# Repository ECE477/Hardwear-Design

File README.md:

# Hardwear Design
Schematic and PCB

## PCB Checklist
### 1 Parts Completion Check
- [x] All major componenets included (ie. Micro, Power Supply, Regulation, Battery Management, IMU, GPS, LoRa, TOLED, Push Buttons, Reset Button, Signal LEDS)
- [x] All support components included (ie. Micro minimum connections, Testing Circuit, Support components package and value(R,Caps,Ind), Application circuits)
#### Other
- [x] Progamming Header 
- [x] Reset Circuit
- [x] Power Connectors
- [x] Mounting holes
- [x] Heartbeat LED
- [x] Debugging LEDs (Transmit LED)
### 2 PCB Footprint Verification Check
- [x] All parts fir on 1:1 scale printout of PCB
### 3 Parts Placement Check
- [x] Oscillator close to Micro? (N/A)
- [x] Decoupling caps close to/under related ICs?
- [x] Connectors on board edges?
- [x] Parts grouped by system and/or in reasonable way that minimizes routing?
### 4 Mechanical/Space Conflict Check:
- [x] Has x- and y- footprint space around electrical pins and pads of all parts been accounted for?
- [x] Has z-height of all parts been accounted for?
- [x] Has clearance been provided for the bolt heads of all mounting holes?
- [x] Have connectors been placed on the outer edges of boards where appropriate? Are they overhanging edges of boards where appropriate? Are they oriented in the correct direction?
- [x] Are all mounting and mechanical support holes free of traces and other electrical items?
### 5 Routing Completion Check:
- [x] All traces routed? (In Eagle, the ratsnest command will say “nothing to do”)
- [x] Oscillator traces clear of interfering signals?
- [x] Traces of appropriate widths to handle current being passed? (Including power traces)
- [x] Traces entering pads at 90-degree angles (or 45 degree angles, where appropriate)?
### 6 Routing Minimization Check:
- [x] Trace lengths have been minimized where possible?
- [x] Octagonal (45-degree constrained) layout mode has been utilized, where possible?
- [x] Right angles have been removed, except where necessary?
- [x] Acute angles have been eliminated from all board routing?
### 7 Via Minimization Check:
- [x] Vias have been eliminated to extent reasonable?
- [x] Signal planes on opposite sides of boards are connected by vias at reasonable intervals?
- [x] Signal Plane Check:
- [x] Signal planes have been included, where reasonable?
- [x] Analog ground (AGND), has been separated from the main ground net in accordance with microcontroller datasheets?
- [x] Isolation on all signal planes has been set to at least 12 mils?
### 9 Silkscreen check
- [x] Silkscreen labels have been provided for all component IDs and connector signal names?
- [x] Silkscreen labels have been appropriately placed near components, but not on top of pads or pins?
- [x] Pin 1 of all ICs and other polarity-sensitive components (such as diodes) is clearly marked?
- [x] Board silkscreen layer includes course and team number "ECE477 Group <x>"?
- [x] Board silkscreen layer includes names of all team members, if possible?
- [x] Board silkscreen layer includes a descriptive name to identify the board?
- [x] Board silkscreen layer includes a revision number and/or last modified date?
### 10 Gerber Check
- [x] Gerber files have been inspected by a gerber viewer program (e.g. gerbv) to check for any
last-minute software CAM-processing defects

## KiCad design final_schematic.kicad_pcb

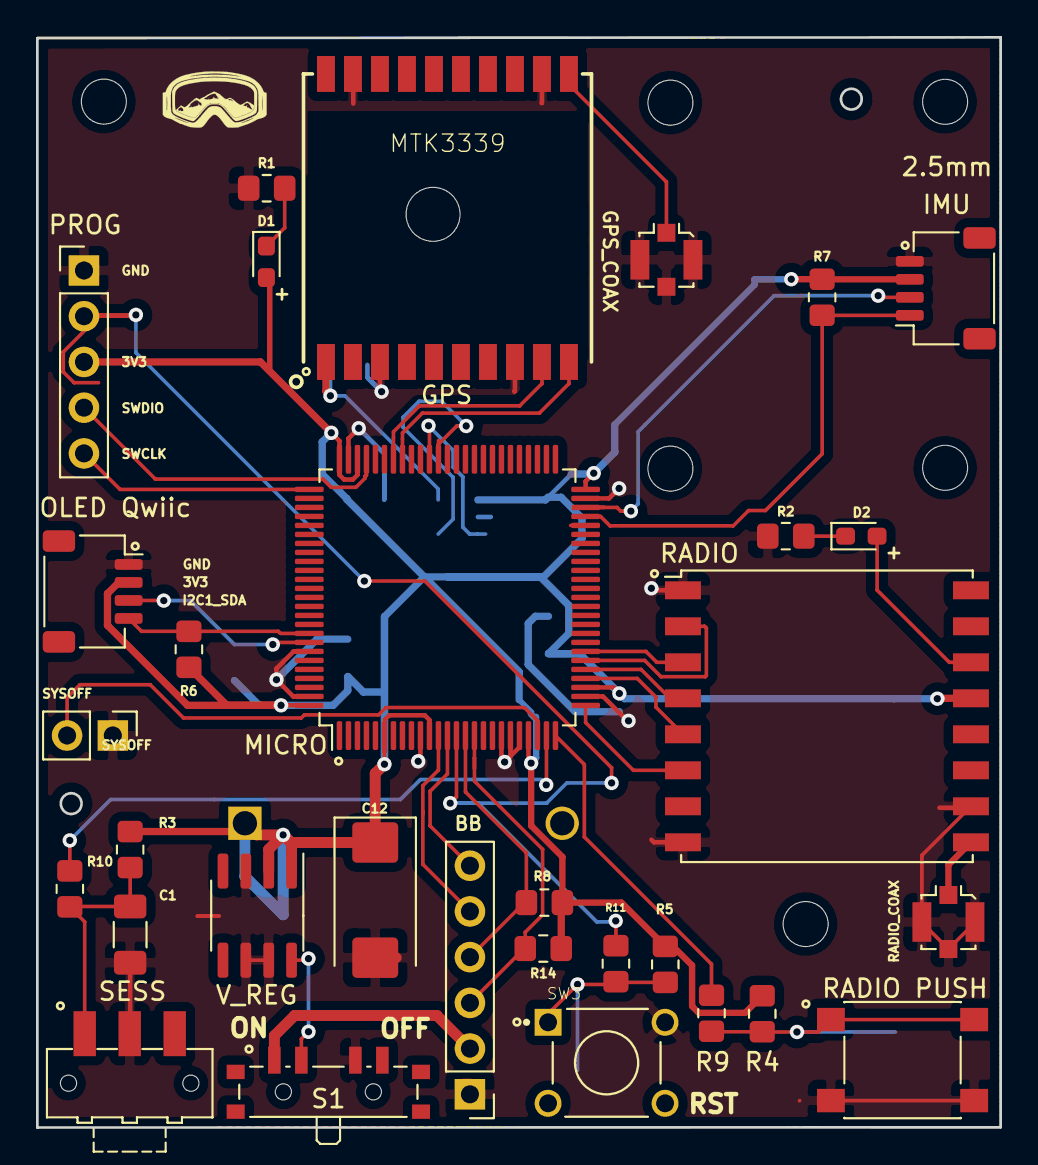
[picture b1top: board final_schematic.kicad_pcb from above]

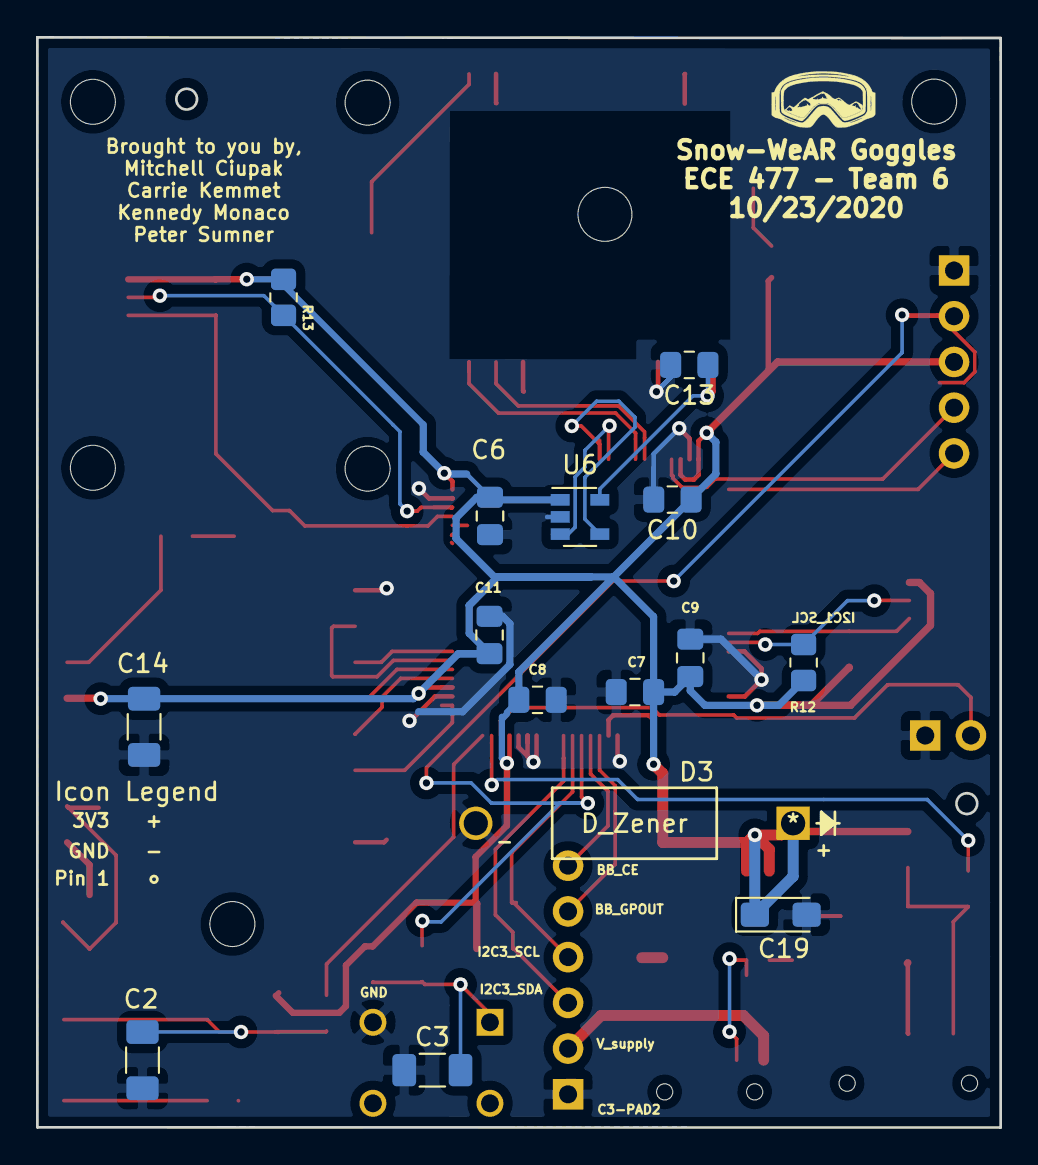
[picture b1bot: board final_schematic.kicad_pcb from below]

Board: 2 copper layers, 53.5 x 60.6 mm, 47 parts (15 on the bottom side), 36 nets.

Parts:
2.5mm: 2.5mm; MountingHole_2.5mm
BB: Battery Babysitter; PinHeader_1x06_P2.54mm_Vertical
C1, C2, C3: 1uF; C_1206_3216Metric_Pad1.33x1.80mm_HandSolder
C6, C7, C8, C9, C10, C11, C13: 0.1uF; C_0805_2012Metric_Pad1.18x1.45mm_HandSolder
C12: 3.3uF; CP_EIA-7343-15_Kemet-W_Pad2.25x2.55mm_HandSolder
C14: 10uF; C_1206_3216Metric_Pad1.33x1.80mm_HandSolder
C19: .1uF; CP_EIA-3216-10_Kemet-I_Pad1.58x1.35mm_HandSolder
D1: LED_HEARTBEAT_R1; D_0603_1608Metric_Pad1.05x0.95mm_HandSolder
D2: LED_TRANSMIT_G1; D_0603_1608Metric_Pad1.05x0.95mm_HandSolder
D3: D_Zener; 1N5355BRLG
GPS: MTK3339; FGPMMOPA6H
IMU: IMU_QWIIC; JST_SH_SM04B-SRSS-TB_1x04-1MP_P1.00mm_Horizontal
J8: GPS_COAX; U.FL_Molex_MCRF_73412-0110_Vertical
MICRO: STM32L476VGTx; LQFP-100_14x14mm_P0.5mm
OLED Qwiic: OLED Qwiic; JST_SH_SM04B-SRSS-TB_1x04-1MP_P1.00mm_Horizontal
PROG: PROG; PinHeader_1x05_P2.54mm_Vertical
R1, R2, R9, R10, R11: 62; R_0805_2012Metric_Pad1.20x1.40mm_HandSolder
R3, R4, R5, R6, R7, R8, R12, R13, R14: 10k; R_0805_2012Metric_Pad1.20x1.40mm_HandSolder
RADIO: RFM95W-868S2; HOPERF_RFM9XW_SMD
RADIO PUSH: SW_Push_RADIO; SW_SPST_PTS645
RADIO_COAX: LoRa_Conn_Coaxial; U.FL_Molex_MCRF_73412-0110_Vertical
S1: ON/OFF-SWITCH; SW_SP3T_PCM13
SESS: SW_Push_SESS; SW_SPDT_CK-JS102011SAQN
SW3: SW_Push_RST; SW_1825910-6-4
SYSOFF: BB_SYSOFF; PinHeader_1x02_P2.54mm_Vertical
U6: TC2014-3.3VxCTTR; SOT-23-5
V_REG: LT1129-3.3_SO8; SOIC-8_3.9x4.9mm_P1.27mm

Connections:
3V3: C6.1, C7.1, C8.1, C9.1, C10.1, C11.1, C12.1, C14.2, C19.1, D1.2, D3.1, IMU.3, MICRO.6, MICRO.11, MICRO.22, MICRO.28, MICRO.50, MICRO.73, MICRO.75, MICRO.100, OLED Qwiic.2, PROG.3, R3.1, R4.1, R5.1, R6.1, R7.1, R8.1, R12.1, R13.1, R14.1, RADIO.13, U6.1, V_REG.1, V_REG.2
BB_CE: BB.6, MICRO.13
BB_GPOUT: BB.5, MICRO.12
BB_Out: S1.2, V_REG.8
CS_LORA: MICRO.29, RADIO.5
DIO0: D2.2, RADIO.14
GND: BB.1, C1.1, C2.1, C3.1, C6.2, C7.2, C8.2, C9.2, C10.2, C11.2, C12.2, C13.2, C14.1, C19.2, D3.2, GPS.3, GPS.8, GPS.12, GPS.19, IMU.4, J8.2, MICRO.10, MICRO.19, MICRO.20, MICRO.21, MICRO.27, MICRO.49, MICRO.74, MICRO.94, MICRO.99, OLED Qwiic.1, PROG.1, R1.1, R2.1, RADIO.1, RADIO.8, RADIO.10, RADIO PUSH.2, RADIO_COAX.2, S1.3, SESS.2, SW3.2, SYSOFF.1, U6.2, V_REG.3, V_REG.6, V_REG.7
GPS_Vin: C13.1, GPS.1, U6.5
I2C1_SCL: MICRO.92, OLED Qwiic.4, R6.2
I2C1_SDA: MICRO.93, OLED Qwiic.3, R12.2
I2C2_SCL: IMU.1, MICRO.47, R7.2
I2C2_SDA: IMU.2, MICRO.48, R13.2
I2C3_SCL: BB.4, MICRO.15, R8.2
I2C3_SDA: BB.3, MICRO.16, R14.2
LDO_ERR: MICRO.64, U6.4
LDO_SHDN: MICRO.65, U6.3
LoRa_RST: MICRO.26, RADIO.6
NRST: MICRO.14, PROG.2, R11.1
unnamed: C1.2, R3.2, R10.2, SESS.1
unnamed: C2.2, R4.2, R9.2, RADIO PUSH.1
unnamed: C3.2, R5.2, R11.2, SW3.1
unnamed: D1.1, R1.2
unnamed: D2.1, R2.2
unnamed: GPS.11, J8.1
unnamed: RADIO.9, RADIO_COAX.1
SPI1_MISO: MICRO.31, RADIO.2
SPI1_MOSI: MICRO.32, RADIO.3
SPI1_SCK: MICRO.30, RADIO.4
SWCLK: MICRO.76, PROG.5
SWDIO: MICRO.72, PROG.4
SYSOFF: MICRO.23, SYSOFF.2
USART_RX: GPS.9, MICRO.69
USART_TX: GPS.10, MICRO.68
V_supply: BB.2, S1.1
radio_btn: MICRO.25, R9.1
session_btn: MICRO.24, R10.1

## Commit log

2020-10-02 first schematic commit
2020-10-06 made original draft look neater. Now I need to actually do work
2020-10-06 Added connectors for battery babysitter and jtag debugger
2020-10-06 added buttons, switch, and 2 leds. Do not have led specs so still need resistor values
2020-10-06 included session push this time. Still ugly
2020-10-07 adding checklist
2020-10-07 README.md -> PCB Checklist
2020-10-07 hi Kennedy
2020-10-07 last minute backup before adding oled headers
2020-10-07 schematic finalized
2020-10-07 netlist added
2020-10-07 Minor changes to Schematic
2020-10-07 micro train!
2020-10-07 no space on the micro train
2020-10-07 pls no more
2020-10-07 Updated footprint assignments
2020-10-07 added footprint library for GPS antenna and chip
2020-10-07 Footprint Assignments Completed
2020-10-07 PCB created
2020-10-07 Grouped Circuits/Re-arranged Schematic
2020-10-08 Updated Schematic from K improvements, also renamed
2020-10-08 all footprints added to .kicad_pcb
2020-10-08 Component Check Passed
2020-10-08 IMU, LORA, and GPS organized
2020-10-08 BB Pin Updates and Flag Updates
2020-10-08 Deleted unnecessary back-up
2020-10-08 Components spacialy assocsiated
2020-10-08 Pre AI Routing Backup
2020-10-08 preperation for the robotic wars
2020-10-08 grounds and 3v3 mapped
2020-10-08 Schematic edits
2020-10-09 schematic partial fix
2020-10-09 added voltage regulator because we need it
2020-10-09 remove gps led
2020-10-11 Schematic Update... again new file: 1825910-6.lib new file: 1825910-6.pro modified: final_schematic-cache.lib modified: final_schematic.sch new file: final_schematic.sch-bak new file: final_schematic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
2020-10-11 Schematic Update with correct resistor values modified: final_schematic.sch modified: final_schematic.sch-bak
2020-10-11 Update final_schematic.sch
    fixed EOL error
2020-10-12 pcb checkpoint
2020-10-12 PCB deconstruction
2020-10-12 latest and greatest
2020-10-13 Update final_schematic.sch
    Removing EOL
2020-10-13 added larger footprints and zener diode
2020-10-13 Schematic FINAL modified: final_schematic-cache.lib modified: final_schematic.sch modified: final_schematic.sch-bak
2020-10-13 Please be right
2020-10-13 I think this is going well
2020-10-13 yep real well
2020-10-13 Routing Complete
2020-10-13 Fill Added REVERT LOCATION
2020-10-13 dimensions finalized
2020-10-13 Design Rules Pass, more silkskin
2020-10-13 Silkscreen is milkscreen
2020-10-13 minor changes
2020-10-13 read update
2020-10-19 Cha Cha Cha Changes
2020-10-21 Todd Meeting Edits
2020-10-22 component update
2020-10-22 keepout
2020-10-22 silkscreen changes
2020-10-22 routing minimization
2020-10-22 routing minimization peer review
2020-10-23 final design, pre gerber
2020-10-23 readme update
2020-10-23 gerber files generated
2020-10-23 gerbv confirmed and scale for imu breakout
2020-10-23 renaming
2020-10-27 fits babysitter now
2020-10-28 gerber update
2020-11-12 latest

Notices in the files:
parts and their libraries:
Copyright 2016 Accelerated Designs. All rights reserved.
